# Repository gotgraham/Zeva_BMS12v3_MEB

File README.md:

# Zeva_BMS12v3_MEB
Zeva BMS12v3 firmware modified to support the VW MEB temperature sensors

This build of the firmware assumes a 10k NTC 3380K B sensor

_To build the firmware, CD to /Firmware and run:_

**$ make**

_This step is only required for new, unprogrammed modules:_

**$ avrdude -c usbtiny -p m16m1 -U lfuse:w:0xFF:m**

_To flash the BMS module with the new firmware_

**$ avrdude -c usbtiny -p m16m1 -U flash:w:Zeva_BMS12_v3.hex**

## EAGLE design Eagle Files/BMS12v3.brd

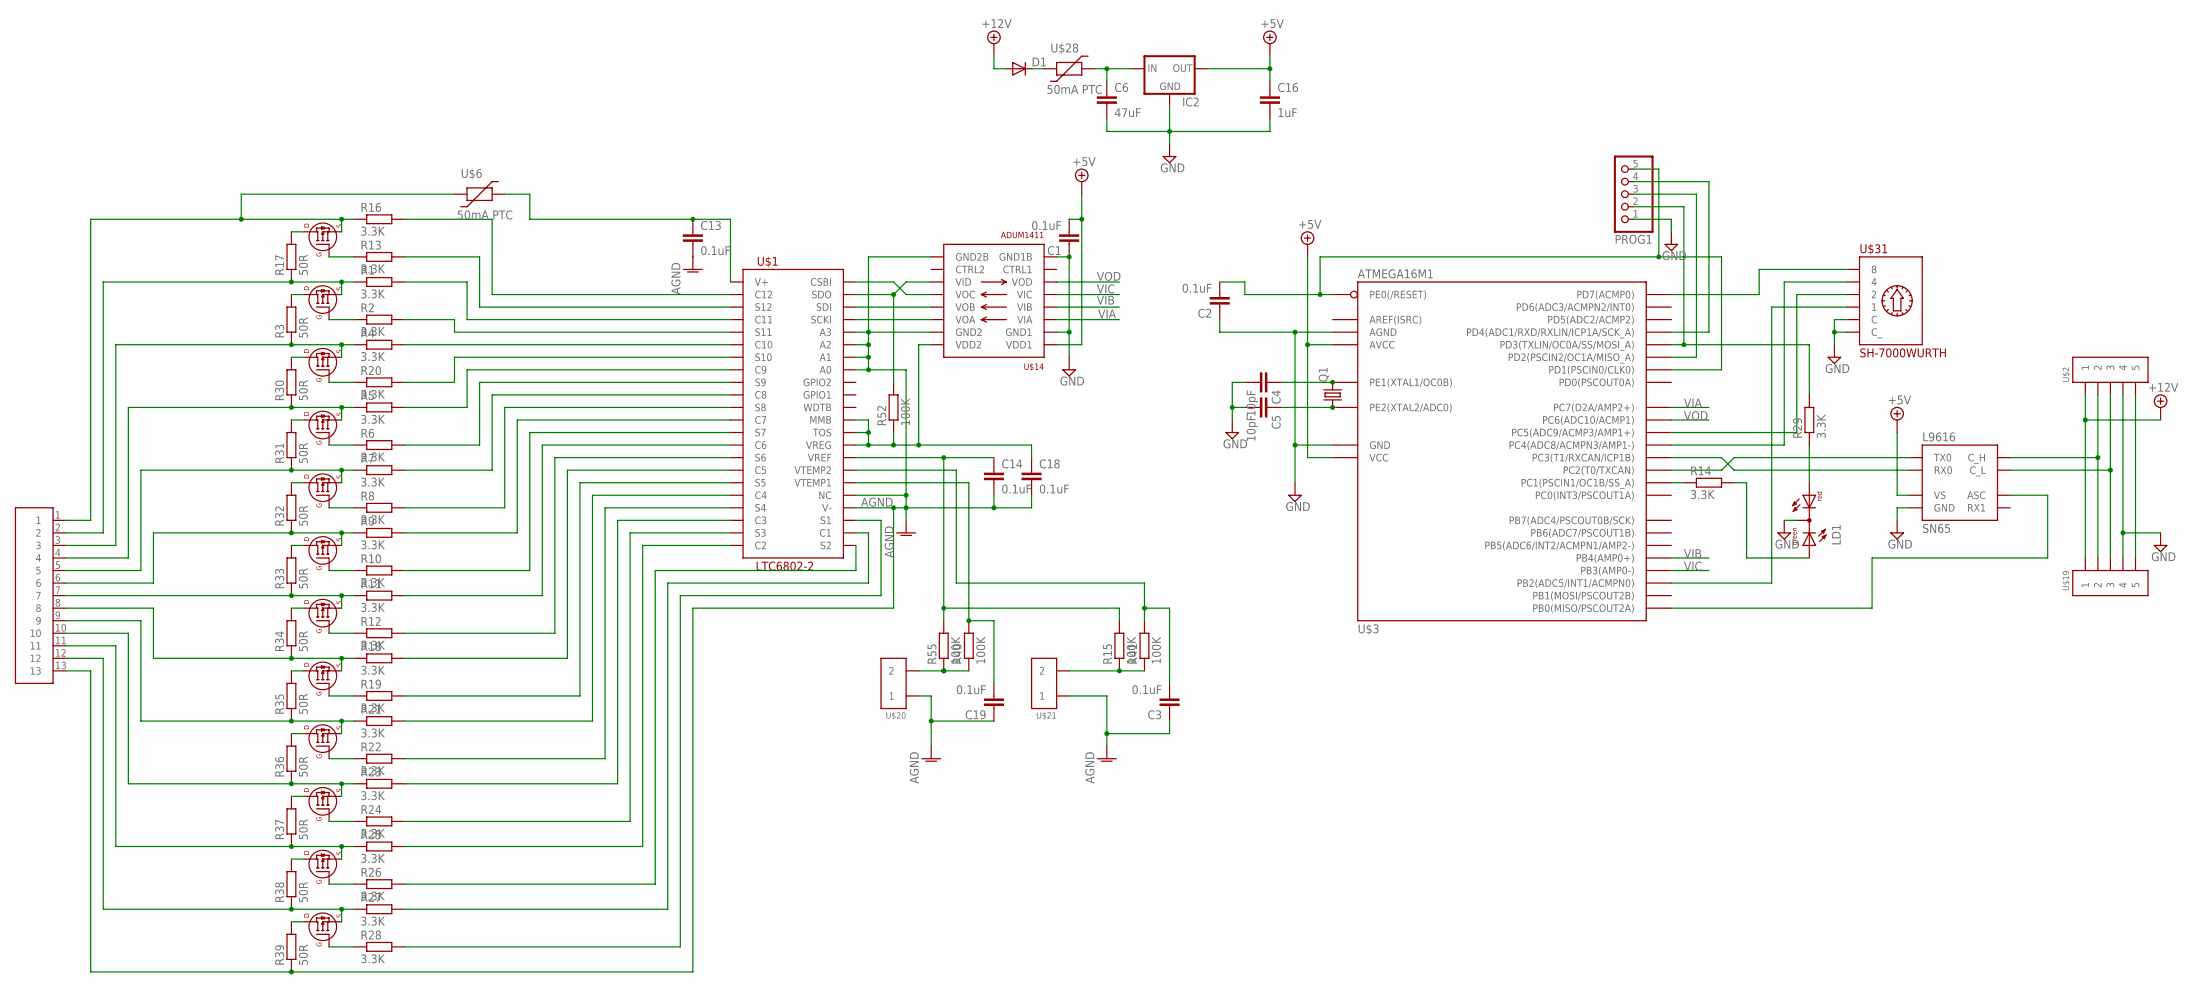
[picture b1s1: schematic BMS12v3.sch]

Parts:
C1, C2, C3, C13, C14, C18, C19: 0.1uF; C0805
C4, C5: 10pF; C0805
C6: 47uF; C1206
C16: 1uF; C0805
D1: DIODE-SOD123; SOD123
IC2: 78LXXSOT89; SOT89R
LD1: DUOLED-RG-C; DUOLED-C-5MM
PROG1: PINHD-1X5; 1X05
Q1: CRYSTALCTS406; CTS406
R1, R2, R4, R5, R6, R7, R8, R9, R10, R11, R12, R13, R14, R16, R18, R19, R20, R21, R22, R23, R24, R25, R26, R27, R28, R29: 3.3K; R0805
R3, R17, R30, R31, R32, R33, R34, R35, R36, R37, R38, R39: 50R; R2512
R15, R40, R41, R52, R55: 100K; R0805
SN65: L9616; SOIC8
U$1: LTC6802-2; SSOP-44
U$2, U$19: MOLEX-39502-1005
U$3: ATMEGA16M1; TQFP32
U$4, U$5, U$7, U$8, U$9, U$10, U$11, U$12, U$13, U$15, U$16, U$17: SI2351DS; SOT23
U$6, U$28: 50mA PTC; 1206
U$14: ADUM1411; SOIC16W
U$18: MOLEX_TERM_BLOCK_13
U$20, U$21: MOLEX-39502-1002
U$31: SH-7000WURTH; WS-ROTV

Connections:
+5V: C1.2, C16.1, IC2.2 (OUT), SN65.P$3 (VS), U$3.4 (VCC), U$3.19 (AVCC), U$14.1 (VDD1)
+12V: D1.A, U$2.1, U$19.1
AGND: C3.1, C13.2, C14.2, C18.2, C19.1, R39.1, U$1.26 (V-), U$1.27 (NC), U$1.37 (A0), U$1.38 (A1), U$1.39 (A2), U$1.40 (A3), U$14.9 (GND2B), U$14.15 (GND2), U$18.13, U$20.1, U$21.1
GND: C1.1, C2.1, C4.2, C5.2, C6.2, C16.2, IC2.4 (GND), LD1.C, PROG1.1, SN65.P$2 (GND), U$2.4, U$3.5 (GND), U$3.20 (AGND), U$14.2 (GND1), U$14.8 (GND1B), U$19.4, U$31.C, U$31.C2 (C_)
unnamed: D1.C, U$28.P$1
unnamed: R16.2, U$1.2 (C12)
unnamed: R13.2, U$1.3 (S12)
unnamed: R3.2, U$5.P$3 (D)
unnamed: R1.2, U$1.4 (C11)
unnamed: R1.1, R17.1, U$5.P$2 (S), U$18.2
unnamed: U$1.42 (SDI), U$14.13 (VOB)
unnamed: R3.1, R4.1, U$7.P$2 (S), U$18.3
unnamed: R4.2, U$1.6 (C10)
unnamed: R26.2, U$1.23 (S2)
unnamed: U$1.41 (SCKI), U$14.14 (VOA)
unnamed: R27.2, U$1.24 (C1)
unnamed: R28.2, U$1.25 (S1)
unnamed: R2.2, U$1.5 (S11)
unnamed: R52.2, U$1.43 (SDO), U$14.11 (VID)
unnamed: U$1.44 (CSBI), U$14.12 (VOC)
unnamed: R2.1, U$5.P$1 (G)
unnamed: R30.2, U$7.P$3 (D)
unnamed: C2.2, PROG1.5, U$3.31 (PE0(/RESET)), U$3.32 (PD1(PSCIN0/CLK0))
unnamed: C6.1, IC2.1 (IN), U$28.P$2
unnamed: R5.2, U$1.8 (C9)
unnamed: R7.2, U$1.10 (C8)
unnamed: R9.2, U$1.12 (C7)
unnamed: R11.2, U$1.14 (C6)
unnamed: C18.1, R52.1, U$1.31 (VREG), U$1.32 (TOS), U$1.33 (MMB), U$14.16 (VDD2)
unnamed: R18.2, U$1.16 (C5)
unnamed: R21.2, U$1.18 (C4)
unnamed: R23.2, U$1.20 (C3)
unnamed: R25.2, U$1.22 (C2)
unnamed: SN65.P$8 (ASC), U$3.8 (PB0(MISO/PSCOUT2A))
unnamed: R5.1, R30.1, U$8.P$2 (S), U$18.4
unnamed: PROG1.2, R29.2, U$3.2 (PD3(TXLIN/OC0A/SS/MOSI_A))
unnamed: PROG1.3, U$3.1 (PD2(PSCIN2/OC1A/MISO_A))
unnamed: PROG1.4, U$3.12 (PD4(ADC1/RXD/RXLIN/ICP1A/SCK_A))
unnamed: SN65.P$4 (RX0), U$3.7 (PC3(T1/RXCAN/ICP1B))
unnamed: SN65.P$1 (TX0), U$3.6 (PC2(T0/TXCAN))
unnamed: SN65.P$7 (C_H), U$2.2, U$19.2
unnamed: SN65.P$6 (C_L), U$2.3, U$19.3
unnamed: LD1.AX (AG), R14.2
unnamed: R14.1, U$3.3 (PC1(PSCIN1/OC1B/SS_A))
unnamed: U$3.15 (PD7(ACMP0)), U$31.8
unnamed: U$3.16 (PB2(ADC5/INT1/ACMPN0)), U$31.1
unnamed: U$3.17 (PC4(ADC8/ACMPN3/AMP1-)), U$31.4
unnamed: U$3.18 (PC5(ADC9/ACMP3/AMP1+)), U$31.2
unnamed: C3.2, R41.2, U$1.29 (VTEMP2)
unnamed: U$2.5, U$19.5
unnamed: C4.1, Q1.3 (2), U$3.10 (PE1(XTAL1/OC0B))
unnamed: C5.1, Q1.1, U$3.11 (PE2(XTAL2/ADC0))
unnamed: R17.2, U$4.P$3 (D)
unnamed: R16.1, U$4.P$2 (S), U$6.P$1, U$18.1
unnamed: R13.1, U$4.P$1 (G)
unnamed: R7.1, R31.1, U$9.P$2 (S), U$18.5
unnamed: R31.2, U$8.P$3 (D)
unnamed: R6.1, U$8.P$1 (G)
unnamed: R20.1, U$7.P$1 (G)
unnamed: R8.1, U$9.P$1 (G)
unnamed: R10.1, U$10.P$1 (G)
unnamed: R12.1, U$11.P$1 (G)
unnamed: R28.1, U$17.P$1 (G)
unnamed: R19.1, U$12.P$1 (G)
unnamed: R22.1, U$13.P$1 (G)
unnamed: R24.1, U$15.P$1 (G)
unnamed: R26.1, U$16.P$1 (G)
unnamed: R27.1, R38.1, U$17.P$2 (S), U$18.12
unnamed: C14.1, R15.2, R55.2, U$1.30 (VREF)
unnamed: C19.2, R40.2, U$1.28 (VTEMP1)
unnamed: LD1.AR, R29.1
unnamed: R25.1, R37.1, U$16.P$2 (S), U$18.11
unnamed: R23.1, R36.1, U$15.P$2 (S), U$18.10
unnamed: R38.2, U$16.P$3 (D)
unnamed: R39.2, U$17.P$3 (D)
unnamed: R37.2, U$15.P$3 (D)
unnamed: R21.1, R35.1, U$13.P$2 (S), U$18.9
unnamed: R36.2, U$13.P$3 (D)
unnamed: R18.1, R34.1, U$12.P$2 (S), U$18.8
unnamed: R35.2, U$12.P$3 (D)
unnamed: R11.1, R33.1, U$11.P$2 (S), U$18.7
unnamed: R9.1, R32.1, U$10.P$2 (S), U$18.6
unnamed: R33.2, U$10.P$3 (D)
unnamed: R34.2, U$11.P$3 (D)
unnamed: R32.2, U$9.P$3 (D)
unnamed: R24.2, U$1.21 (S3)
unnamed: R22.2, U$1.19 (S4)
unnamed: R40.1, R55.1, U$20.2
unnamed: R15.1, R41.1, U$21.2
unnamed: R20.2, U$1.7 (S10)
unnamed: R6.2, U$1.9 (S9)
unnamed: R8.2, U$1.11 (S8)
unnamed: R10.2, U$1.13 (S7)
unnamed: R12.2, U$1.15 (S6)
unnamed: R19.2, U$1.17 (S5)
V+: C13.1, U$1.1 (V+), U$6.P$2
VIA: U$3.25 (PC7(D2A/AMP2+)), U$14.3 (VIA)
VIB: U$3.24 (PB4(AMP0+)), U$14.4 (VIB)
VIC: U$3.23 (PB3(AMP0-)), U$14.5 (VIC)
VOD: U$3.22 (PC6(ADC10/ACMP1)), U$14.6 (VOD)

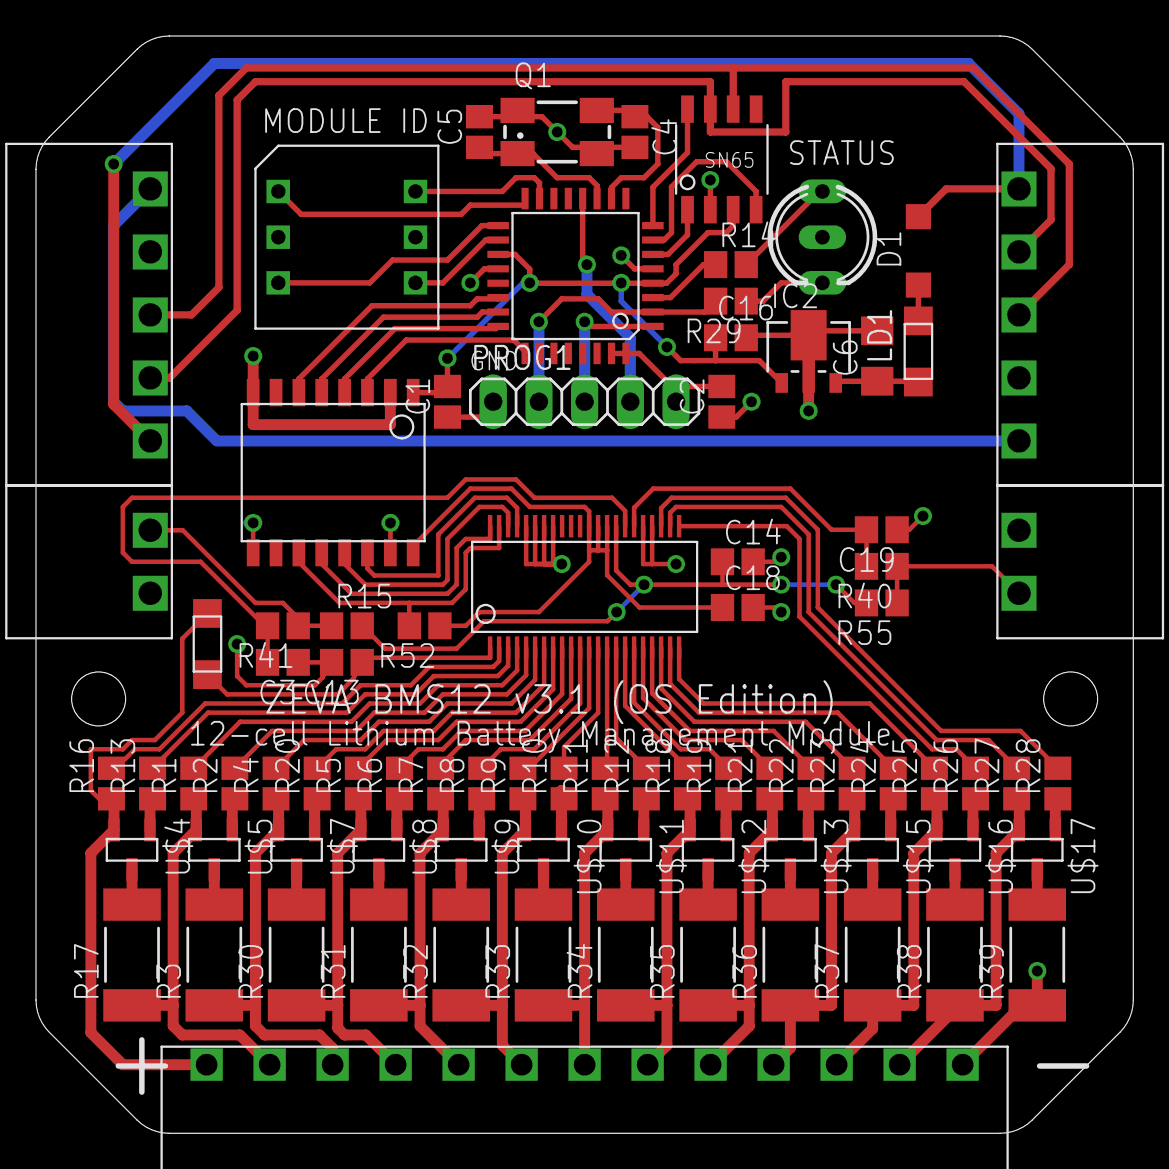
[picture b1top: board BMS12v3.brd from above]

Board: 2 copper layers, 61.0 x 61.0 mm, 83 parts (0 on the bottom side), 100 nets.

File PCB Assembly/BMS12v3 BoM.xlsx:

| #ITEM | Description | Designator | PACKAGE | Manufacturer | Manufacturer Part Number# | Supplier | Supplier Part # | QTY/BOARD | Pads each | Total pads | Holes each | Total holes
 | 1 | Molex 0395021013 | U$18 |  | Molex | 395021013 | Digi-Key | WM7781-ND | 1 |  |  | 13 | 13
 | 2 | 47ohm 1W 5% resistor | R3, R17, R30, R31, R32, R33, R34, R35, R36, R37, R38, R39 | 2512 |  |  |  |  | 12 | 2 | 24
 | 3 | SI2301BDS MOSFET | U$4, U$5, U$7, U$8, U$9, U$10, U$11, U$12, U$13, U$15, U$16, U$17 | TO-236-3 | Vishay Siliconix | SI2301BDS-T1-E3 |  |  | 12 | 3 | 36
 | 4 | 3.3Kohm 1% resistor | R1, R2, R4, R5, R6, R7, R8, R9, R10, R11, R12, R13, R14, R16, R18, R19, R20, R2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 | 0805 |  |  |  |  | 26 | 2 | 52
 | 5 | 0.1uF 50V capacitor | C1, C2, C3, C14, C18, C19 | 0805 |  |  |  |  | 6 | 2 | 12
 | 6 | 100Kohm 1% resistor | R15, R40, R41, R52, R55 | 0805 |  |  |  |  | 5 | 2 | 10
 | 7 | LTC6802-2 | U$1 | 44-FSOP | Linear Technologies | LTC6802IG-2#PBF | Digi-Key | LTC6802IG-2#PBF-ND | 1 | 44 | 44
 | 8 | ADUM1401 | U$14 | 16-SOIC | Analog Devices | ADUM1401ARWZ-RL | Digi-Key | ADUM1401ARWZ-RLCT-ND | 1 | 16 | 16
 | 9 | Molex 0395021005 | U$2, U$19 |  | Molex | 0395021005 | Digi-Key | WM7773-ND | 2 |  |  | 5 | 10
 | 10 | Molex 0395021002 | U$20, U$21 |  | Molex | 0395021002 | Digi-Key | WM7770-ND | 2 |  |  | 2 | 4
 | 11 | 1uF 16V capacitor | C16 | 0805 |  |  |  |  | 1 | 2 | 2
 | 12 | 47uF 16V capacitor | C6 | 1206 |  |  |  |  | 1 | 2 | 2
 | 13 | 50mA PTC fuse | U$6, U$28 | 1206 | Bel Fuse Inc | 0ZCJ0005FF2E | Digi-Key | 507-1793-1-ND | 2 | 2 | 4
 | 14 | L78L05 5V reg | IC2 | TO-243AA | ST | L78L05BUTR | Digi-Key | 497-1181-1-ND | 1 | 3 | 3
 | 15 | BAV3004W diode | D1 | SOD-123 | Diodes Incorporated | BAV3004W-7-F | Digi-Key | BAV3004W-FDICT-ND | 1 | 2 | 2
 | 16 | SN65HVD1040QDRQ1 | SN65 | SOIC-8 | Texas Instruments | SN65HVD1040QDRQ1 | Digi-Key | 296-21592-1-ND | 1 | 8 | 8
 | 17 | 10pF capacitor | C4, C5 | 0805 |  |  |  |  | 2 | 2 | 4
 | 18 | 8Mhz crystal | Q1 | CTS406 | Abracon | ABM3B-8.000MHZ-10-1-U-T | Digi-Key | 535-9721-1-ND | 1 | 4 | 4
 | 19 | 16-way rotary switch | U$31 |  | Wurth Electronics | 428527320916 | Digi-Key | 428527320916-ND | 1 |  |  | 6 | 6
 | 20 | ATmega16M1 | U$3 | 32-TQFP | Microchip Technology | ATMEGA16M1-AU | Digi-Key | ATMEGA16M1-AU-ND | 1 | 32 | 32
 | 21 | 3mm Red/Green LED | LD1 |  | Lite-On Inc | LTL1BEKVJNN | Digi-Key | 160-1939-ND | 1 |  |  | 3 | 3
 | 22 | 0.1uF 100V capacitor | C13 | 0805 |  |  |  |  | 1 | 2 | 2
 |  |  |  |  |  |  |  | TOTALS: | 82 |  | 257 |  | 36

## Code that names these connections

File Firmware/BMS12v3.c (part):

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#define COMMS_TIMEOUT	32 // at 32Hz, i.e 1 second timeout

// SPI interface pins
#define	CSBI		(1<<PB3)
#define CSBI_PORT	PORTB
#define	SDO			(1<<PC6)
#define SDO_PORT	PINC
#define SDI			(1<<PB4)
#define SDI_PORT	PORTB
#define SCKI		(1<<PC7)
#define SCKI_PORT	PORTC

// Status LED
#define GREEN_PORT	PORTC
#define GREEN		(1<<PC1)
#define RED_PORT	PORTD
#define RED			(1<<PD3)

// LTC6802 Command codes
#define WRCFG	0x01
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#define STTMPAD	0x30

// Inputs from hex rotary pot for module ID selection
#define	MOD_ID_NUM8		(PIND & (1<<PD7))
#define MOD_ID_NUM4		(PINC & (1<<PC4))
#define MOD_ID_NUM2		(PINC & (1<<PC5))
#define MOD_ID_NUM1		(PINB & (1<<PB2))

// Function declarations
void SetupPorts();
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
void SetupPorts()
{
	DDRB = 0b00011001; // PB0 = CAN Enable, PB3 = CSBI, PB4 = SDI
	DDRC = 0b10000010; // PC7 = SCKI, PC1 = GREEN LED
	DDRD = 0b00001000; // PD3 = RED LED

	// Pull-ups for module ID selectors
	PORTB = 0b00000100;
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
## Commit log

2025-11-30 Initial
2025-11-30 Fix compiler warnings
2025-11-30 Update firmware for 10k 3389K B NTC sensor
2025-11-30 Add to readme

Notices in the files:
Firmware/BMS12v3.c:
Open Source version, released under MIT License (see Readme file)
